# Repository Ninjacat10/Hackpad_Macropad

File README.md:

# Productivity Pad

A 6-key macropad with a rotary encoder, built for the [Hack Club Hackpad](https://hackpad.hackclub.com/) program.

## Overview

## Schematic

## PCB

## Case

Single-piece, fully 3D printed case (`CAD/hackpad_assembly.step`).

## Bill of Materials

| Ref | Part | Footprint | Qty |
|-----|------|-----------|-----|
| SW1-SW6 | Cherry MX-style switch | `SW_Cherry_MX_1.00u_PCB` | 6 |
| SW8 | Rotary encoder (w/ push switch) | `RotaryEncoder_Alps_EC11E-Switch_Vertical_H20mm` | 1 |
| U1 | Seeeduino XIAO | `XIAO-Generic-Hybrid-14P-2.54-21X17.8MM` | 1 |

Full generated BOM: [production/bom.csv](production/bom.csv)

## Firmware

Runs [KMK](https://github.com/KMKfw/kmk_firmware) on the Seeeduino XIAO. Keys are direct-wired to GPIO pins (no diode matrix). See [Firmware/main.py](Firmware/main.py) for the pin mapping (extracted from the schematic) and keymap.

## Repo structure

```
CAD/        complete case CAD (assembly + individual parts)
PCB/        KiCad project (schematic, PCB, project files)
Firmware/   KMK firmware source
production/ manufacturing files: gerbers.zip, PCB.step, bom.csv
docs/       README images
```

## Building it yourself

1. Order the PCB using [production/gerbers.zip](production/gerbers.zip)
2. 3D print / laser cut the case from [CAD/](CAD/)
3. Flash [Firmware/main.py](Firmware/main.py) to the XIAO via KMK/CircuitPython
4. Assemble and solder switches per the BOM above

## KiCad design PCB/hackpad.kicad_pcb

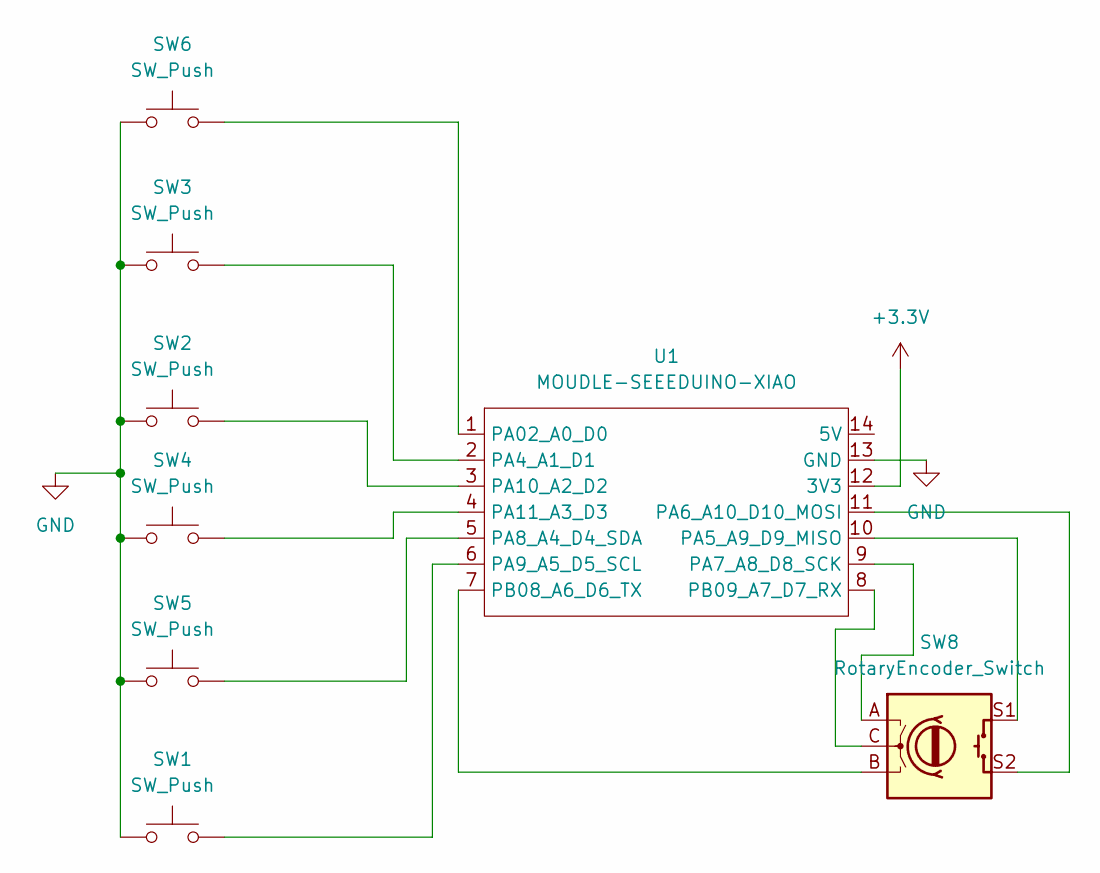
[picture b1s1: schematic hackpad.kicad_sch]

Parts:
SW1, SW2, SW3, SW4, SW5, SW6: SW_Push; SW_Cherry_MX_1.00u_PCB
SW8: RotaryEncoder_Switch; RotaryEncoder_Alps_EC11E-Switch_Vertical_H20mm
U1: MOUDLE-SEEEDUINO-XIAO; XIAO-Generic-Hybrid-14P-2.54-21X17.8MM

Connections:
+3.3V: U1.12 (3V3)
GND: SW1.1, SW2.1, SW3.1, SW4.1, SW5.1, SW6.1, U1.13 (GND)
unnamed: SW6.2, U1.1 (PA02_A0_D0)
unnamed: SW3.2, U1.2 (PA4_A1_D1)
unnamed: SW8.S1, U1.10 (PA5_A9_D9_MISO)
unnamed: SW8.S2, U1.11 (PA6_A10_D10_MOSI)
unnamed: SW8.A, U1.9 (PA7_A8_D8_SCK)
unnamed: SW5.2, U1.5 (PA8_A4_D4_SDA)
unnamed: SW1.2, U1.6 (PA9_A5_D5_SCL)
unnamed: SW2.2, U1.3 (PA10_A2_D2)
unnamed: SW4.2, U1.4 (PA11_A3_D3)
unnamed: SW8.B, U1.7 (PB08_A6_D6_TX)
unnamed: SW8.C, U1.8 (PB09_A7_D7_RX)

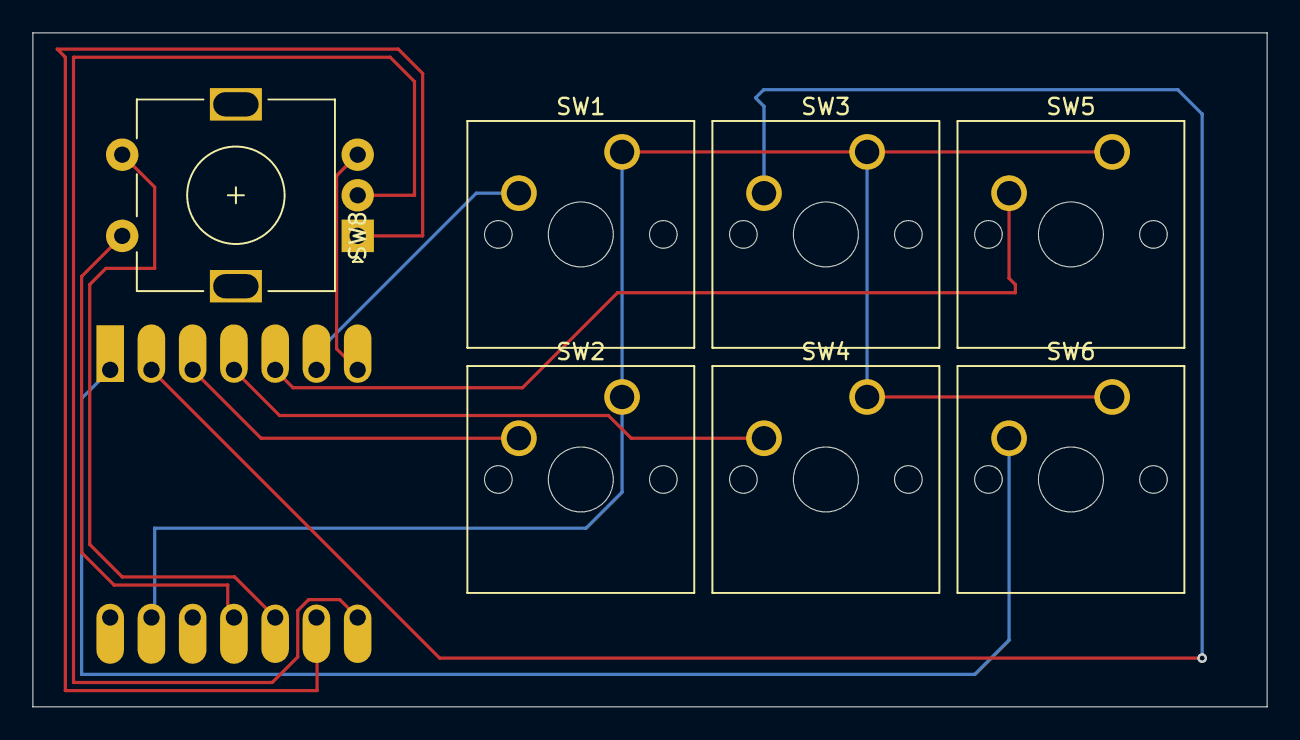
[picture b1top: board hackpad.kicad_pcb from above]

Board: 2 copper layers, 76.0 x 41.5 mm, 8 parts (1 on the bottom side), 12 nets.

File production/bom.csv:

"Reference","Value","Footprint","Qty"
"SW1-SW6","SW_Push","Button_Switch_Keyboard:SW_Cherry_MX_1.00u_PCB",""
"SW8","RotaryEncoder_Switch","Rotary_Encoder:RotaryEncoder_Alps_EC11E-Switch_Vertical_H20mm",""
"U1","MOUDLE-SEEEDUINO-XIAO","footprints:XIAO-Generic-Hybrid-14P-2.54-21X17.8MM",""
